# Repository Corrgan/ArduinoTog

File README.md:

# Betty-Wandler (vormals ArduinoTog)

Arduino-Nano-Platine, um ein **VAG/Audi-Kombiinstrument ab ca. 2000 in ein älteres Auto** einzubauen (hier: Audi-A6-C5-Kombi in einem VW T3 Syncro mit 1.9 TDI).

Ein Nano erledigt drei Aufgaben:

| Funktion | Was sie macht |
|---|---|
| **TOG / Öltemperatur** | Emuliert den pulscodierten Öltemperaturgeber (TOG), den das Kombi erwartet – auf Basis eines normalen VW-Öltemperaturfühlers (A1). Keine Warnungen, Anzeige funktioniert. |
| **Tankanzeige** | Liest den originalen (alten) Tankgeber (A2) und steuert den Tankeingang des Kombis über ein schaltbares Widerstandsnetz (PhotoMOS-Relais). Die Kennlinie wird per USB eingemessen und im EEPROM gespeichert. |
| **Warnleuchten-Ausgang** | Open-Drain-Ausgang (D5, MOSFET), der eine Warnleuchten-Leitung des Kombis (z. B. ABS) nach Masse ziehen kann. |

> ⚠️ **Stand: Entwurf, noch nicht gebaut oder im Fahrzeug getestet** (v1, Nov. 2026). Nutzung auf eigene Gefahr – das Ding hängt an der Fahrzeugelektrik.

## Aufbau des Repos

```
firmware/betty_wandler/    Arduino-Sketch (Nano, ATmega328P)
hardware/pcb/              KiCad-9-Platine, Generator-Skript, JLCPCB-Fertigungsdaten (Gerber-ZIP, BOM, CPL)
hardware/enclosure/        OpenSCAD-Gehäuse + STLs (Unterteil mit M5-Laschen, Deckel mit Lüftungsschlitzen)
docs/                      Schaltplan, Anschlussplan (PDF), Bau- und Einmess-Anleitung (LIESMICH.txt)
legacy/                    die ursprünglichen ArduinoTog-Sketches
```

## Schnellstart

1. Platine bestellen (2 Lagen, 2,0 mm, bestückt) mit den Dateien aus `hardware/pcb/fertigung/` – Details in `docs/LIESMICH.txt`.
2. `firmware/betty_wandler/betty_wandler.ino` auf einen Arduino Nano flashen.
3. Anschließen wie in `docs/anschlussplan.pdf`.
4. Per USB einmessen (Serieller Monitor, 115200 Baud): `ohm <wert>`, `hier <i> <ohm>`, `tabelle`, `speichern`, `auto`.

## Danke

- [BlackBrix/TinyTOG](https://github.com/BlackBrix/TinyTOG) für die ursprüngliche TOG-Recherche und -Logik.
- gnif (hostfission) fürs Korrigieren und Erklären des ersten Codes.

Lizenz: GPL-3.0 (siehe `LICENSE`).

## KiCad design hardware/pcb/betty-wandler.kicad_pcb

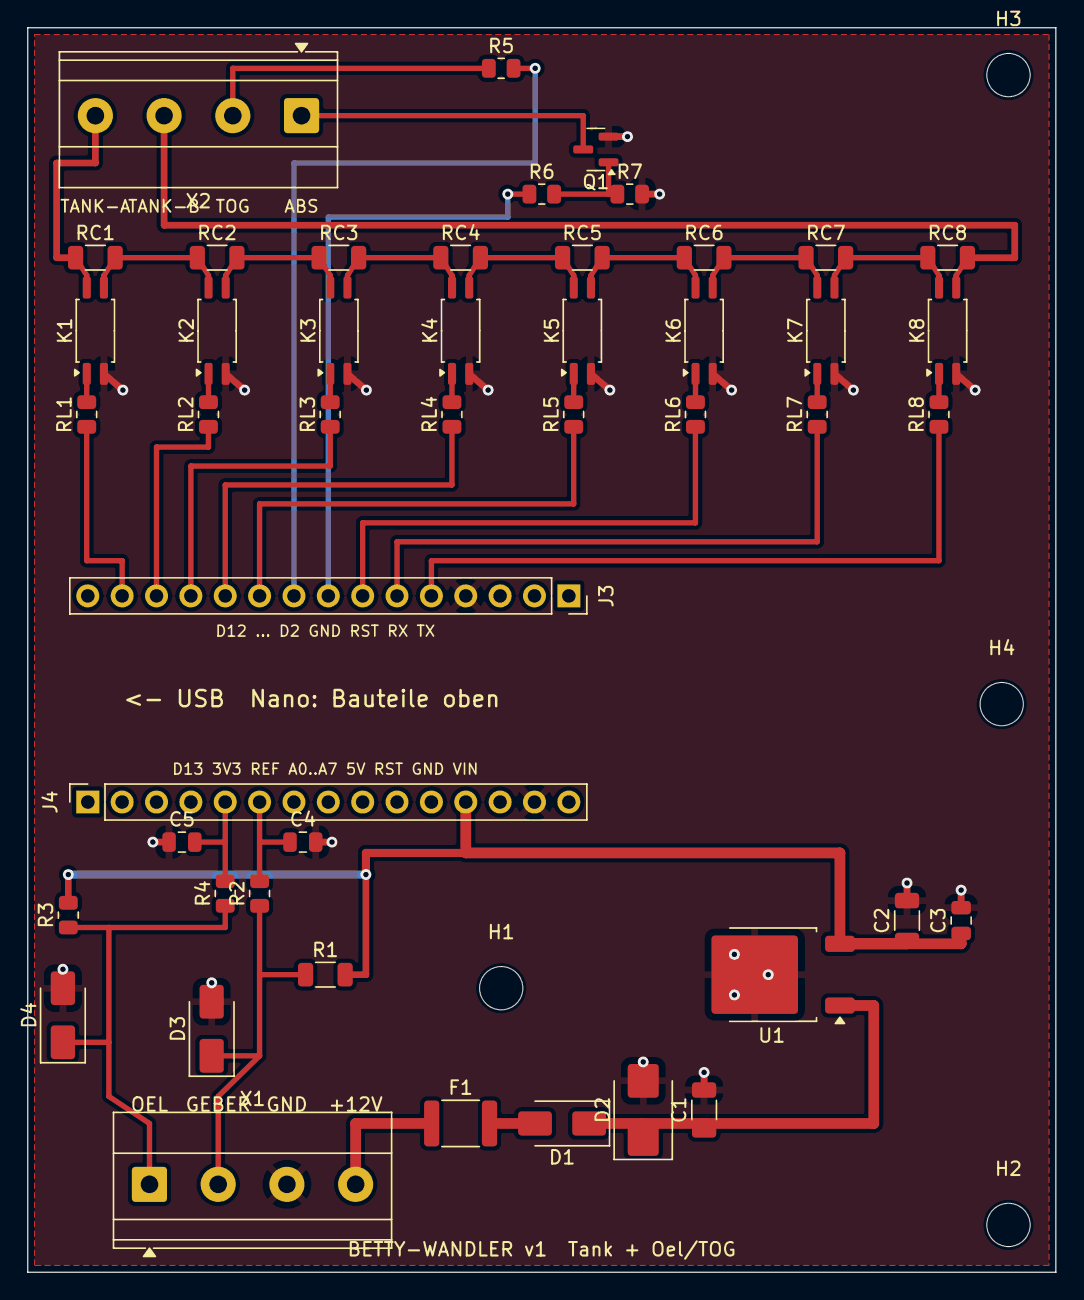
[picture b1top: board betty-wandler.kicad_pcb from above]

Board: 2 copper layers, 76.0 x 92.0 mm, 51 parts (0 on the bottom side), 39 nets.

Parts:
C1: 10u 50V; C_1206_3216Metric
C2: 10u 25V; C_1206_3216Metric
C3, C4, C5: 100n; C_0805_2012Metric
D1: SS34; D_SMA
D2: SMBJ24A; D_SMB
D3, D4: SMAJ5.0A; D_SMA
F1: PTC 0.5A; Fuse_1812_4532Metric
H1, H2, H3, H4: MountingHole_3.2mm_M3
J3: Nano 1-15; PinSocket_1x15_P2.54mm_Vertical
J4: Nano 16-30; PinSocket_1x15_P2.54mm_Vertical
K1, K2, K3, K4, K5, K6, K7, K8: AQY212GS; SOP-4_4.4x2.6mm_P1.27mm
Q1: 2N7002; SOT-23
R1: 150R; R_1206_3216Metric
R2, R4: 10k; R_0805_2012Metric
R3, R5: 1k; R_0805_2012Metric
R6: 100R; R_0805_2012Metric
R7: 100k; R_0805_2012Metric
RC1: 270R; R_1206_3216Metric
RC2: 130R; R_1206_3216Metric
RC3: 62R; R_1206_3216Metric
RC4: 33R; R_1206_3216Metric
RC5: 16R; R_1206_3216Metric
RC6: 8R2; R_1206_3216Metric
RC7: 3R9; R_1206_3216Metric
RC8: 2R0; R_1206_3216Metric
RL1, RL2, RL3, RL4, RL5, RL6, RL7, RL8: 470R; R_0805_2012Metric
U1: L78M05; TO-252-2
X1: Oel|Geber|GND|+12V; TerminalBlock_Phoenix_MKDS-1,5-4-5.08_1x04_P5.08mm_Horizont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
X2: Kombi A|B|TOG|ABS; TerminalBlock_Phoenix_MKDS-1,5-4-5.08_1x04_P5.08mm_Horizont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

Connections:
12V_F: D1.2, F1.2
12V_P: C1.1, D1.1, D2.1, U1.1
+5V: C2.1, C3.1, J4.12, R1.2, R3.2, U1.3
+12V: F1.1, X1.4
A1: C5.2, J4.5, R4.2
A2: C4.1, J4.6, R2.2
ABS: Q1.3, X2.1
D2: J3.5, RL8.1
D3: J3.6, RL7.1
D4: J3.7, RL6.1
D5: J3.8, R6.1
D6: J3.9, R5.2
D7: J3.10, RL5.1
D8: J3.11, RL4.1
D9: J3.12, RL3.1
D10: J3.13, RL2.1
D11: J3.14, RL1.1
GATE: Q1.1, R6.2, R7.1
GEBER: D3.1, R1.1, R2.1, X1.2
GND: C1.2, C2.2, C3.2, C4.2, C5.1, D2.2, D3.2, D4.2, J3.4, J4.14, K1.2, K2.2, K3.2, K4.2, K5.2, K6.2, K7.2, K8.2, Q1.2, R7.2, U1.2, X1.3
KETTE0: K1.4, RC1.1, X2.4
KETTE1: K1.3, K2.4, RC1.2, RC2.1
KETTE2: K2.3, K3.4, RC2.2, RC3.1
KETTE3: K3.3, K4.4, RC3.2, RC4.1
KETTE4: K4.3, K5.4, RC4.2, RC5.1
KETTE5: K5.3, K6.4, RC5.2, RC6.1
KETTE6: K6.3, K7.4, RC6.2, RC7.1
KETTE7: K7.3, K8.4, RC7.2, RC8.1
KETTE8: K8.3, RC8.2, X2.3
LED_D2: K8.1, RL8.2
LED_D3: K7.1, RL7.2
LED_D4: K6.1, RL6.2
LED_D7: K5.1, RL5.2
LED_D8: K4.1, RL4.2
LED_D9: K3.1, RL3.2
LED_D10: K2.1, RL2.2
LED_D11: K1.1, RL1.2
OEL: D4.1, R3.1, R4.1, X1.1
TOG: R5.1, X2.2

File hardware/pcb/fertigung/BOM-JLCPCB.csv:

Comment,Designator,Footprint,LCSC Part #
Keramikkondensator 10u 50V X7R 1206,C1,1206,
Keramikkondensator 10u 25V X7R 1206,C2,1206,
Keramikkondensator 100n X7R 0805,"C3,C4,C5",0805,
SS34 Schottky 40V 3A,D1,SMA,
SMBJ24A TVS-Diode unidirektional,D2,SMB,
SMAJ5.0A TVS-Diode unidirektional,"D3,D4",SMA,
PTC-Sicherung 1812 0.5A hold (z. B. 1812L050),F1,1812,
Buchsenleiste 1x15 2.54mm gerade (THT),"J3,J4",PinSocket 1x15,
PhotoMOS-Relais 60V 1.1A SOP-4 (Panasonic AQY212GS oder G3VM-61A1/AQY212EH),"K1,K2,K3,K4,K5,K6,K7,K8",SOP-4,
2N7002 N-MOSFET 60V,Q1,SOT-23,
Widerstand 150Ω 1% 1206,R1,1206,
Widerstand 10kΩ 1% 0805,"R2,R4",0805,
Widerstand 1kΩ 1% 0805,"R3,R5",0805,
Widerstand 100Ω 1% 0805,R6,0805,
Widerstand 100kΩ 1% 0805,R7,0805,
Widerstand 270Ω 1% 1206,RC1,1206,
Widerstand 130Ω 1% 1206,RC2,1206,
Widerstand 62Ω 1% 1206,RC3,1206,
Widerstand 33Ω 1% 1206,RC4,1206,
Widerstand 16Ω 1% 1206,RC5,1206,
Widerstand 8.2Ω 1% 1206,RC6,1206,
Widerstand 3.9Ω 1% 1206,RC7,1206,
Widerstand 2.0Ω 1% 1206,RC8,1206,
Widerstand 470Ω 1% 0805,"RL1,RL2,RL3,RL4,RL5,RL6,RL7,RL8",0805,
L78M05CDT-TR 5V 0.5A Längsregler,U1,TO-252-2,
"Schraubklemme 4-pol 5.08mm (Phoenix MKDS 1,5/4-5,08 oder KF128-5.08-4P)","X1,X2",TB 4P 5.08,

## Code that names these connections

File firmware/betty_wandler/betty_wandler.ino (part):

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#include <EEPROM.h>

// ---------------- Pins ----------------
const uint8_t PIN_TOG = 6, PIN_ABS = 5;
const uint8_t PIN_OEL = A1, PIN_GEBER = A2;
const uint8_t RELAIS[8] = {2, 3, 4, 7, 8, 9, 10, 11};                 // überbrücken RC8..RC1
const float   R_KETTE[8] = {2.0, 3.9, 8.2, 16.0, 33.0, 62.0, 130.0, 270.0}; // Ω, zu RELAIS[i]
const float   R_ON = 1.0;            // PhotoMOS-Durchlasswiderstand (Datenblatt typ. ~0,8–2 Ω)
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// Platzhalter bis zum Einmessen: T2-Richtwert (10 Ω voll … 73 Ω leer) → A5-Richtwert (65 Ω voll … 280 Ω leer)
void tabelleStandard() {
  tab.magic = MAGIC; tab.n = 2;
  tab.geber[0] = 10;  tab.kombi[0] = 65;
  tab.geber[1] = 73;  tab.kombi[1] = 280;
}

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// ---------------- Hilfen ----------------
float leseGeberOhm() {
  long s = 0;
  for (uint8_t i = 0; i < 16; i++) s += analogRead(PIN_GEBER);
  float u = s / 16.0;                                   // 0 … 1023
  if (u >= 1022) return 9999;                           // Geber offen
  return R_PULLUP_GEBER * u / (1023.0 - u);
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  if (jetzt - togStart < togDauer) return;
  togStart = jetzt;
  switch (togPhase) {
    case 0: digitalWrite(PIN_TOG, HIGH); togDauer = 20000UL;                 togPhase = 1; break;
    case 1: digitalWrite(PIN_TOG, LOW);  togDauer = LOW_US[oelStufe];        togPhase = 2; break;
    case 2: digitalWrite(PIN_TOG, HIGH); togDauer = HIGH_US[oelStufe];       togPhase = 3; break;
    default: digitalWrite(PIN_TOG, LOW); togDauer = 250000UL;                togPhase = 0; break;
  }
}

void leseOel() {
  long s = 0;
  for (uint8_t i = 0; i < 8; i++) s += analogRead(PIN_OEL);
  oelRoh = s / 8;
  uint8_t st = NUM_LEVELS - 1;
  for (uint8_t i = 0; i < NUM_LEVELS; i++) if (oelRoh >= ANALOG_VALUES[i]) { st = i; break; }
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
// ---------------- Setup / Loop ----------------
void setup() {
  pinMode(PIN_TOG, OUTPUT); digitalWrite(PIN_TOG, LOW);
  pinMode(PIN_ABS, OUTPUT); digitalWrite(PIN_ABS, HIGH);       // MOSFET an → ABS-Leitung an Masse (wie bisher D5 LOW)
  for (uint8_t i = 0; i < 8; i++) { pinMode(RELAIS[i], OUTPUT); digitalWrite(RELAIS[i], LOW); }
  Serial.begin(115200);
  EEPROM.get(0, tab);
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
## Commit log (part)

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2025-08-31 Update arduino_tog_new.ino with the new content
